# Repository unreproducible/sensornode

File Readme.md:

# SensorNode - Development Board

This is a board mostly intended to make a high quality environmental sensor
(BME280 or BME680) available via the magic of "IoT".  The board has some
interesting features that should make it good for training, teaching, or just
general IoT uses:
* ESP32
    * Wifi
    * Bluetooth
    * 4MB Flash
* BME280 / BME680 Support
  * Temperature
  * Pressure 
  * Humidity
* TSL2591
    * Full Spectrum Light Sensor
    * IR Spectrum Light Sensor
* MicroSD card slot
* LiPo battery support (charging and discharging)
* CP2104 USB <-> Serial Port
* Working Good Display E-ink support (specifically 2.13in screens)
    * v1.2 or later

# Getting Started
The following link is a presentation that was done in 2018 specifically targetting this board

https://events.linuxfoundation.org/wp-content/uploads/2017/12/osseu18_-_discovering_tiny_snakes_John-Hawley.pdf

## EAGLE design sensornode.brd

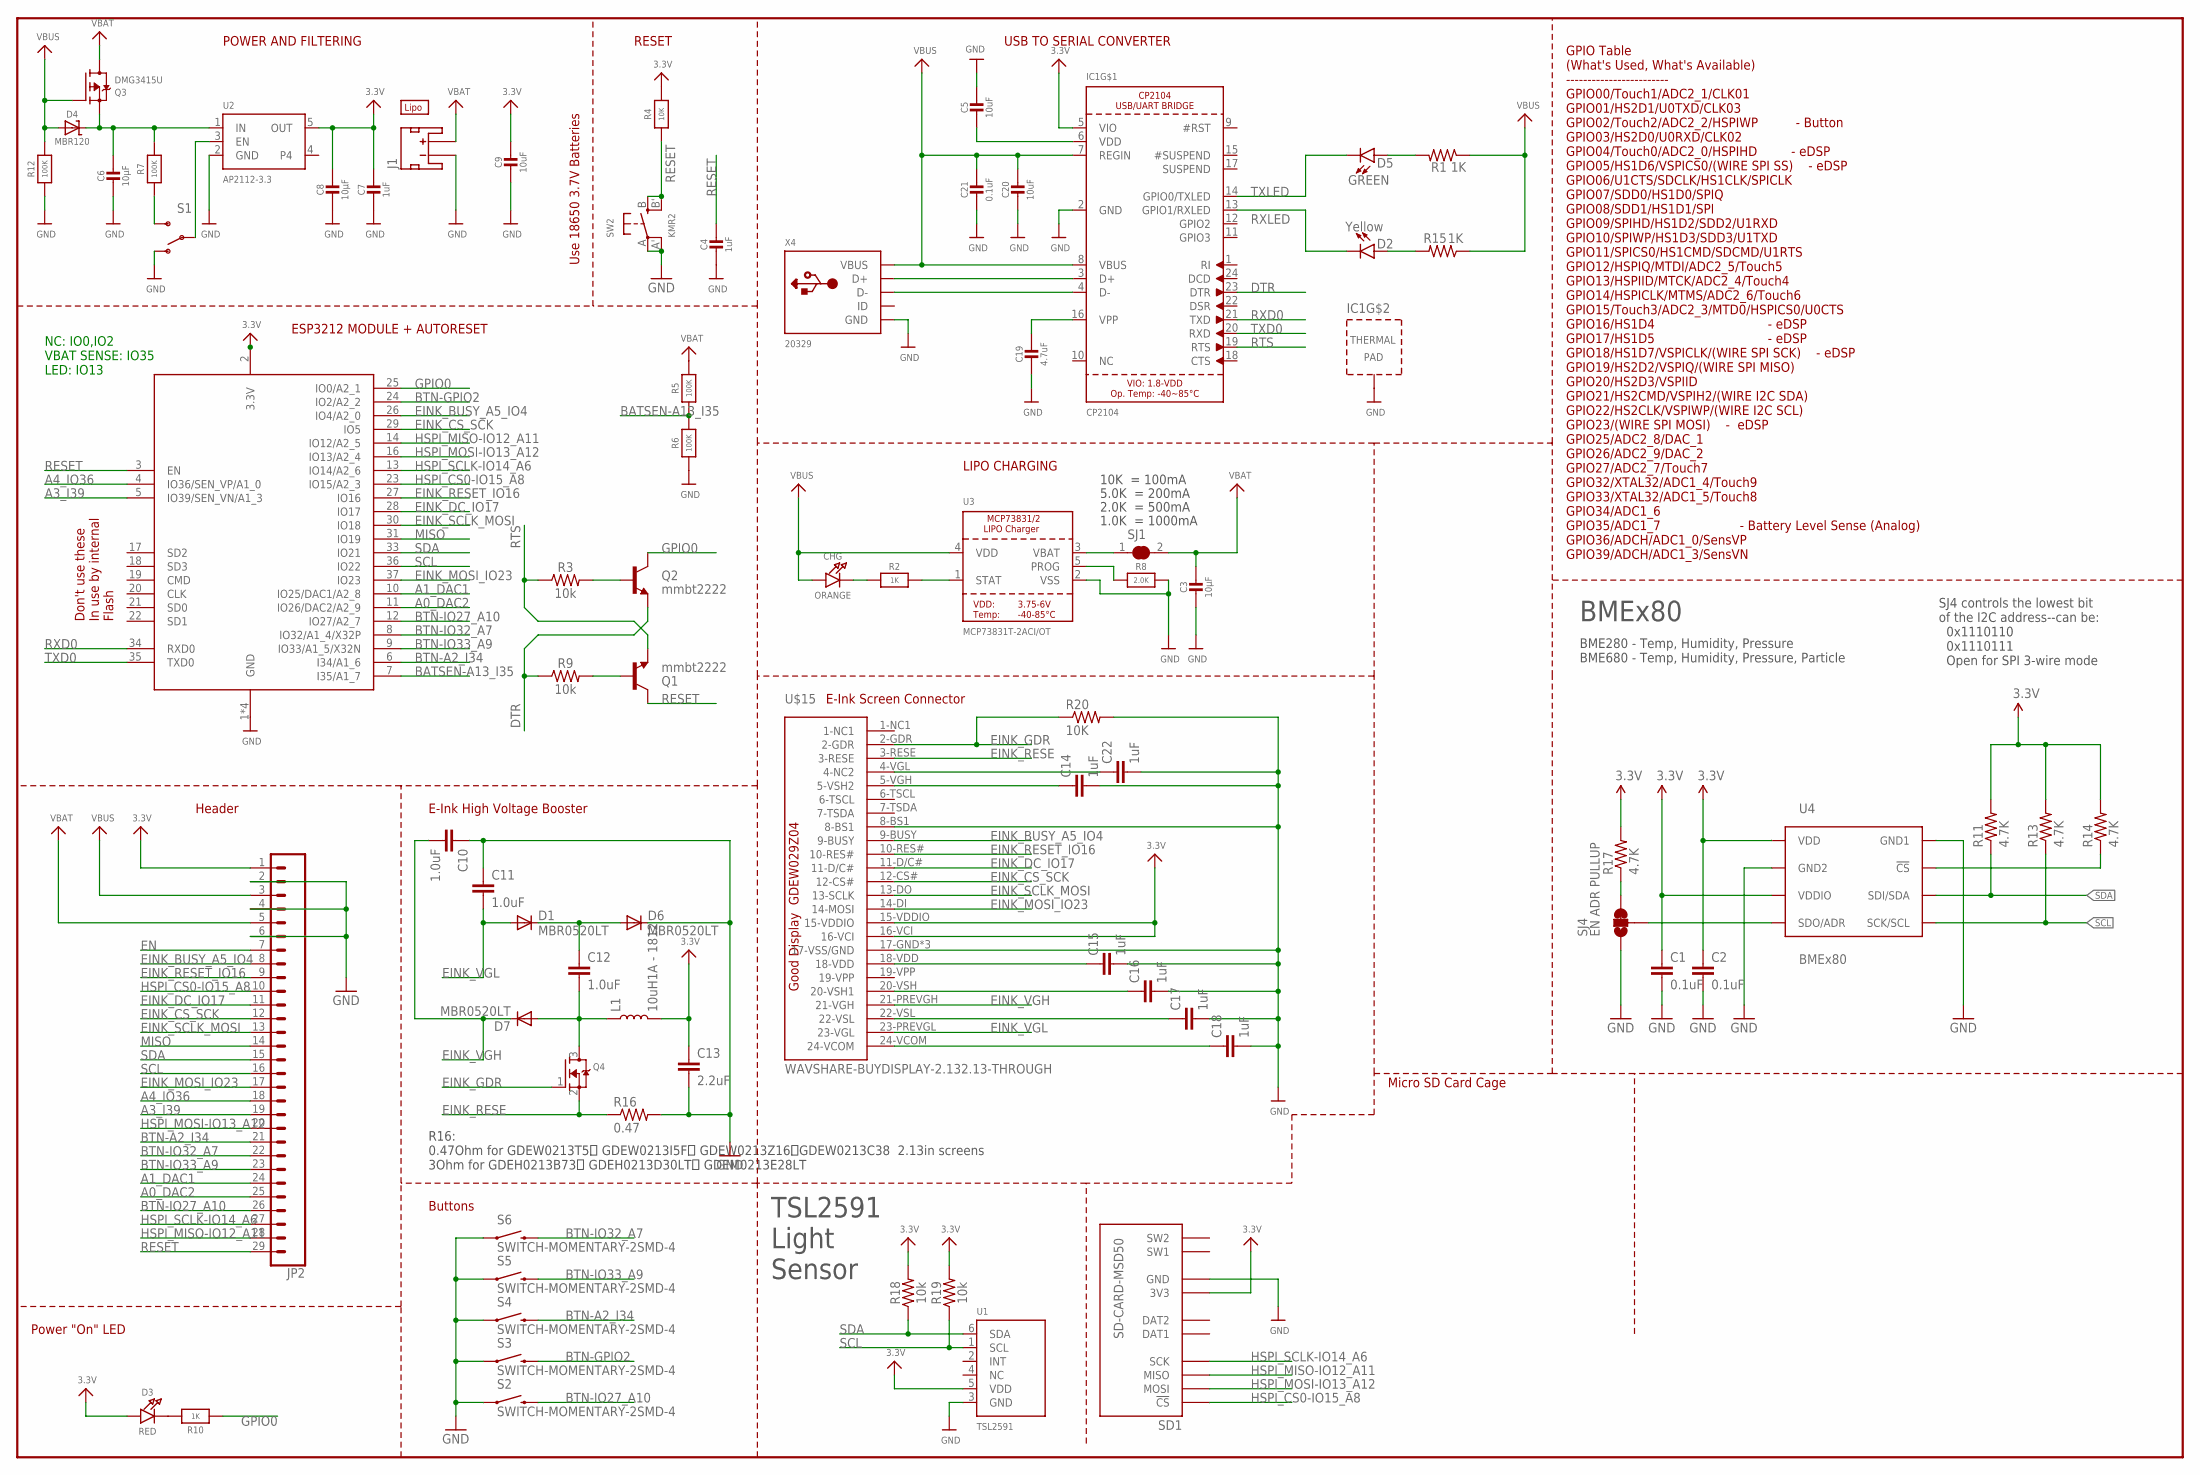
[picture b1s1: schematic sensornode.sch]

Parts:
BT1: LIPO-OUTLINE2000; LIPO-2000
C1, C2: 0.1uF; 0603-CAP
C3, C6, C8: 10µF; 0805-NO
C4, C7: 1uF; 0603-NO
C5, C9, C20: 10uF; 0805-NO
C10, C11, C12: 1.0uF; 0603
C13: 2.2uF; 0603
C14, C15, C16, C17, C18, C22: 1uF; 0603-CAP
C19: 4.7uF; 0805-NO
C21: 0.1uF; 0805-NO
CHG: ORANGE; CHIPLED_0805_NOOUTLINE
D1, D6, D7: MBR0520LT; SOD123
D2: Yellow; LED-0603
D3: RED; CHIPLED_0805_NOOUTLINE
D4: MBR120; SOD-123
D5: GREEN; LED-0603
IC1: CP2104; QFN24_4MM_SMSC
J1: JST_2MM_MALE; JST-2-SMD
JP2: CONN_29; 1X29
L1: 10uH1A - 1812; 1815
Q1, Q2: mmbt2222; SOT23-3
Q3: DMG3415U; SOT23-R
Q4: MOSFET-NREFLOW; SOT23
R1, R15: 1K; 0603-RES
R2, R10: 1K; 0603-NO
R3, R9, R18, R19: 10k; 0603
R4: 10K; 0603-NO
R5, R6, R7, R12: 100K; 0603-NO
R8: 2.0K; 0603-NO
R11, R13, R14, R17: 4.7K; 0603-RES
R16: 0.47; 0603-RES
R20: 10K; 0603-RES
S1: SWITCH-SPDT-SMD-A; SWITCH-SPST-SMD-A
S2, S3, S4, S5, S6: SWITCH-MOMENTARY-2SMD-4; TACTILE_SWITCH_TALL
SD1: SD-CARD-MSD50; SD_5031821853
SJ1: SOLDERJUMPER_CLOSED; SOLDERJUMPER_CLOSEDWIRE@1
SJ4: EN ADR PULLUP; PAD-JUMPER-3-2OF3_NC_BY_TRACE_YES_SILK_FULL_BOX
SW2: KMR2; BTN_KMR2_4.6X2.8
U1: TSL2591; DFN6_TAOS
U2: AP2112-3.3; SOT23-5
U3: MCP73831T-2ACI/OT; SOT23-5
U4: BMEx80; BME280_LGA
U$15: WAVSHARE-BUYDISPLAY-2.132.13-THROUGH; WAVSHARE-BUYDISPLAY-2.13-THM
X2: ESP32_WROOM32_SKINNY; WROOM32_SKINNY
X4: 20329; MICRO-USB5+6P-SMD-0.65-B

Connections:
3.3V: C1.1, C2.1, C7.1, C8.1, C9.1, C13.1, D3.A, IC1.5 (VIO), JP2.1, L1.2, R1.1, R4.2, R11.2, R13.2, R14.2, R15.1, R17.2, R18.2, R19.2, SD1.VCC (3V3), U1.5 (VDD), U2.5 (OUT), U4.P$6 (VDDIO), U4.P$8 (VDD), U$15.15-VDDIO, U$15.16-VCI, X2.2 (3.3V)
!CS: R14.1, U4.P$2 (!CS)
A0_DAC2: JP2.25, X2.11 (IO26/DAC2/A2_9)
A1_DAC1: JP2.24, X2.10 (IO25/DAC1/A2_8)
A3_I39: JP2.19, X2.5 (IO39/SEN_VN/A1_3)
A4_IO36: JP2.18, X2.4 (IO36/SEN_VP/A1_0)
BATSEN-A13_I35: R5.1, R6.2, X2.7 (I35/A1_7)
BTN-A2_I34: JP2.21, S4.B2 (2), X2.6 (I34/A1_6)
BTN-GPIO2: S3.B2 (2), X2.24 (IO2/A2_2)
BTN-IO27_A10: JP2.26, S2.B2 (2), X2.12 (IO27/A2_7)
BTN-IO32_A7: JP2.22, S6.B2 (2), X2.8 (IO32/A1_4/X32P)
BTN-IO33_A9: JP2.23, S5.B2 (2), X2.9 (IO33/A1_5/X32N)
DTR: IC1.23 (DTR), Q2.2 (E), R9.1
EINK_BUSY_A5_IO4: JP2.8, U$15.9-BUSY, X2.26 (IO4/A2_0)
EINK_CS_SCK: JP2.12, U$15.12-CS#, X2.29 (IO5)
EINK_DC_IO17: JP2.11, U$15.11-D/C#, X2.28 (IO17)
EINK_GDR: Q4.1 (G), R20.1, U$15.2-GDR
EINK_MOSI_IO23: JP2.17, U$15.14-DI (14-MOSI), X2.37 (IO23)
EINK_RESE: Q4.2 (S), R16.1, U$15.3-RESE
EINK_RESET_IO16: JP2.9, U$15.10-RES#, X2.27 (IO16)
EINK_SCLK_MOSI: JP2.13, U$15.13-DO (13-SCLK), X2.30 (IO18)
EINK_VGH: C10.2, D7.C, U$15.21-PREVGH (21-VGH)
EINK_VGL: C11.2, D1.A, U$15.23-PREVGL (23-VGL)
EN: JP2.7, S1.2, U2.3 (EN)
GND: C1.2, C2.2, C3.2, C4.2, C5.1, C6.2, C7.2, C8.2, C9.2, C10.1, C11.1, C13.2, C14.2, C15.2, C16.2, C17.2, C18.2, C19.2, C20.2, C21.2, C22.2, D6.C, IC1.2 (GND), IC1.THERM (TP), J1.1 (-), JP2.2, JP2.4, JP2.6, R6.1, R8.2, R12.1, R16.2, R20.2, S1.1 (O), S2.A2 (1), S3.A2 (1), S4.A2 (1), S5.A2 (1), S6.A2 (1), SD1.GND, SJ4.1, SW2.A, SW2.A' (P1), U1.3 (GND), U2.2 (GND), U3.2 (VSS), U4.P$1 (GND1), U4.P$7 (GND2), U$15.8-BS1, U$15.17-GND (17-VSS/GND), U$15.25 (17-VSS/GND), U$15.26 (17-VSS/GND), X2.1 (GND), X2.15 (GND), X2.38 (GND), X2.P$1 (GND), X4.5 (GND), X4.S1 (GND), X4.S2 (GND), X4.S3 (GND), X4.S4 (GND), X4.S5 (GND), X4.S6 (GND)
GPIO0: Q2.3 (C), R10.1, X2.25 (IO0/A2_1)
HSPI_CS0-IO15_A8: JP2.10, SD1.CS (!CS), X2.23 (IO15/A2_3)
HSPI_MISO-IO12_A11: JP2.28, SD1.MISO, X2.14 (IO12/A2_5)
HSPI_MOSI-IO13_A12: JP2.20, SD1.MOSI, X2.16 (IO13/A2_4)
HSPI_SCLK-IO14_A6: JP2.27, SD1.SCK, X2.13 (IO14/A2_6)
MISO: JP2.14, X2.31 (IO19)
unnamed: CHG.C, R2.1
unnamed: R8.1, U3.5 (PROG)
unnamed: R2.2, U3.1 (STAT)
unnamed: R7.1, S1.3 (S)
unnamed: D3.C, R10.2
unnamed: C5.2, IC1.6 (VDD)
unnamed: C6.1, D4.C, Q3.2 (S), R7.2, U2.1 (IN)
unnamed: D5.A, R1.2
unnamed: SJ1.1, U3.3 (VBAT)
unnamed: D2.A, R15.2
unnamed: C12.1, D1.C, D6.A
unnamed: Q1.1 (B), R9.2
unnamed: Q2.1 (B), R3.2
unnamed: C12.2, D7.A, L1.1, Q4.3 (D)
unnamed: R17.1, SJ4.3
unnamed: C15.1, U$15.18-VDD
unnamed: C16.1, U$15.20-VSH (20-VSH1)
unnamed: C17.1, U$15.22-VSL
unnamed: C18.1, U$15.24-VCOM
unnamed: C14.1, U$15.5-VGH (5-VSH2)
unnamed: C19.1, IC1.16 (VPP)
unnamed: C22.1, U$15.4-VGL (4-NC2)
RESET: C4.1, JP2.29, Q1.3 (C), R4.1, SW2.B (S), SW2.B' (S1), X2.3 (EN)
RTS: IC1.19 (RTS), Q1.2 (E), R3.1
RXD0: IC1.21 (TXD), X2.34 (RXD0)
RXLED: D2.C, IC1.13 (GPIO1/RXLED)
SCL: JP2.16, R13.1, R19.1, U1.1 (SCL), U4.P$4 (SCK/SCL), X2.36 (IO22)
SDA: JP2.15, R11.1, R18.1, U1.6 (SDA), U4.P$3 (SDI/SDA), X2.33 (IO21)
SDO/ADR: SJ4.2, U4.P$5 (SDO/ADR)
TXD0: IC1.20 (RXD), X2.35 (TXD0)
TXLED: D5.C, IC1.14 (GPIO0/TXLED)
USBD_N: IC1.4 (D-), X4.2 (D-)
USBD_P: IC1.3 (D+), X4.3 (D+)
VBAT: C3.1, J1.2 (+), JP2.5, Q3.3 (D), R5.2, SJ1.2
VBUS: C20.1, C21.1, CHG.A, D4.A, IC1.7 (REGIN), IC1.8 (VBUS), JP2.3, Q3.1 (G), R12.2, U3.4 (VDD), X4.1 (VBUS)

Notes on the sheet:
POWER AND FILTERING
RESET
10K = 100mA
5.0K = 200mA
2.0K = 500mA
1.0K = 1000mA
USB TO SERIAL CONVERTER
LIPO CHARGING
Power "On" LED
GPIO Table (What's Used, What's Available) ------------------------ GPIO00/Touch1/ADC2_1/CLK01 GPIO01/HS2D1/U0TXD/CLK03 GPIO02/Touch2/ADC2_2/HSPIWP - Button GPIO03/HS2D0/U0RXD/CLK02 GPIO04/Touch0/ADC2_0/HSPIHD - eDSP GPIO05/HS1D6/VSPICS0/(WIRE SPI SS) - eDSP GPIO06/U1CTS/SDCLK/HS1CLK/SPICLK GPIO07/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
Header
Buttons
Use 18650 3.7V Batteries
ESP3212 MODULE + AUTORESET
NC: IO0,IO2 VBAT SENSE: IO35 LED: IO13
Don't use these In use by internal Flash
E-Ink High Voltage Booster
TSL2591 Light Sensor
BMEx80
SJ4 controls the lowest bit of the I2C address--can be: 0x1110110 0x1110111 Open for SPI 3-wire mode
BME280 - Temp, Humidity, Pressure BME680 - Temp, Humidity, Pressure, Particle
E-Ink Screen Connector
Micro SD Card Cage
R16: 0.47Ohm for GDEW0213T5、 GDEW0213I5F、 GDEW0213Z16、GDEW0213C38 2.13in screens 3Ohm for GDEH0213B73、 GDEH0213D30LT、 GDEM0213E28LT

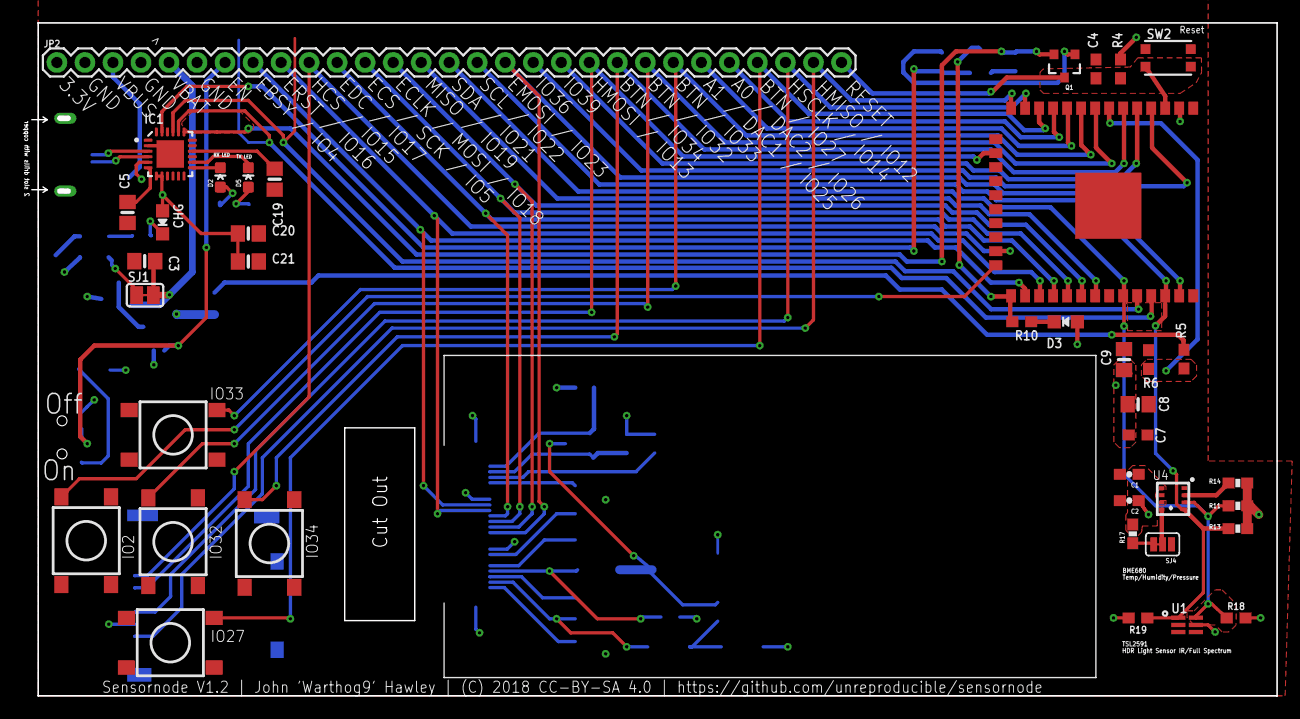
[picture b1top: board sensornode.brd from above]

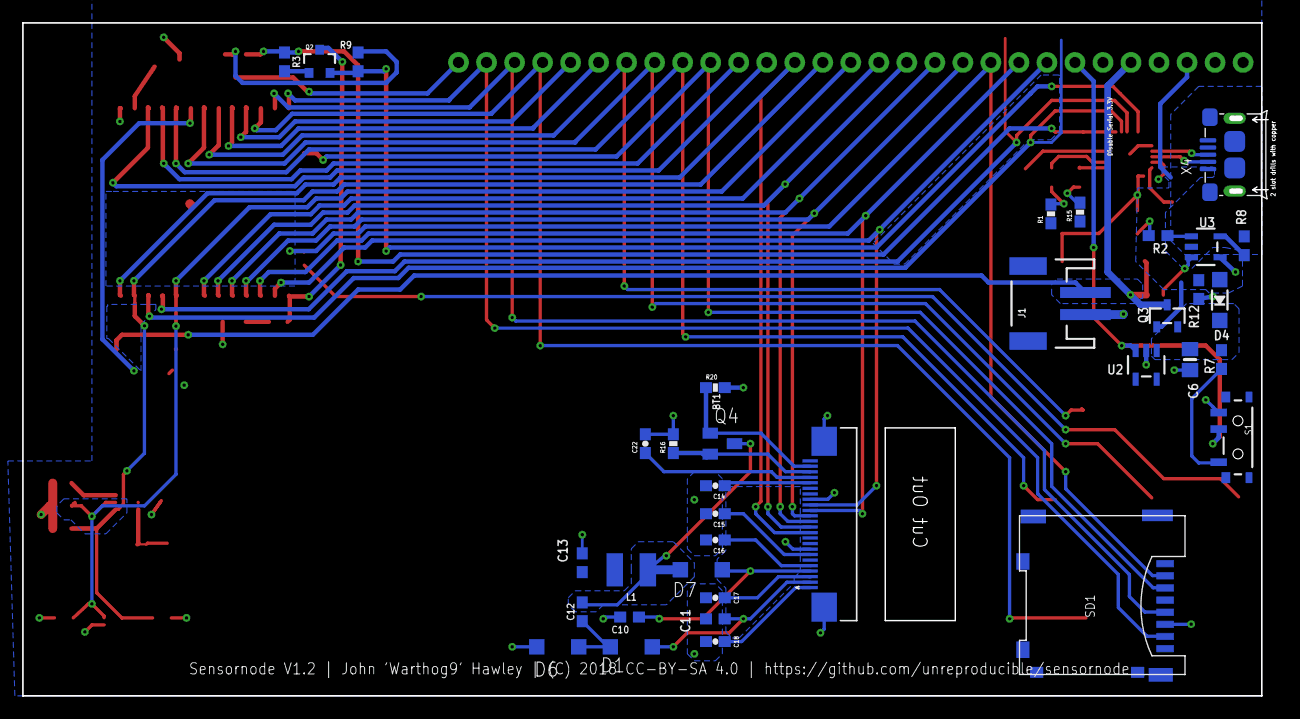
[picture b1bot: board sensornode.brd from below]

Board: 2 copper layers, 112.9 x 61.0 mm, 76 parts (36 on the bottom side), 66 nets.

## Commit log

2016-12-18 Adding the schematic
2016-12-19 Updating schematic, and initial layout
2016-12-19 Updating with latest routing attempt
2016-12-19 Fixing ear routing
    it's tighter now, but it's a lot better for obvious reasons
2016-12-20 Reworking things + the ESP12S is lacking pins present on the schematic (doh)
2016-12-20 Finishing up for the night, think this is all routed now
2016-12-20 more cleanups
2016-12-24 Adding in the colateral used for the silkscreen
2016-12-24 Finally moved things around enough to make it all work
2016-12-25 Just adding some silk
2016-12-25 more silkscreen stuff
2016-12-25 clearing out all the stupid # files
2016-12-27 more silk changes
2017-01-07 Initial sensor board work
2017-06-27 Initial commit for ESP32 conversion
2018-02-05 Initial, full, routing - minus Sensors, update gitignore
2018-02-15 Mostly Routed - saving and pushing up
2018-03-10 Big changes - 'final' routing, light sensor, bme280 -> bme680
2018-03-10 Renaming the board and schematic to actually match the project
2018-03-10 Updating the License information
2018-03-10 Cleaning up some text
2018-03-10 Board: Show all layers
2018-03-10 Adding board image and pdf schematic
2018-03-11 Adjusting parts based on BOM generation
    So there were a bunch of duplicated 0603 and 0805 parts, unifying
    things to 0603s
2018-03-28 USB-UART: switch to "USB Powered"
    This changes the USB chip from being powered via the
    regulated 3.3V line off the board, to being powered
    via the USB VBUS power. This should basically disable
    the chip when the USB isn't plugged in.
2018-04-02 BRD: updating the accepted DRC issues
2018-04-05 Adjusting the keepout around the antennae
2018-04-06 USB: Swapping the USB part out - twas unobtanium
    the 4UCONN connector that Adafruit used is basically made of unobtanium
    and more or less doesn't exist. The part that was trying to be used
    the rear prongs did not match up by any stretch of the imagination.
    A mess of e-mails an annoyance ensued.
    I'm swapping out the part on everything I can now, this seems to be
    more common, and there's parts that are similar enough to it that
2018-04-25 Moving sensors down-making room for wifi keep out
2018-04-25 Clearing some space around the eink screen
2018-04-25 increase board height to 61mm
    Also adjust some parts near the top
2018-04-25 Adjusting board width
2018-05-06 Getting the updates in
    Yes, this is a terrible commit
2018-05-14 Adjusting some signal names
2018-07-17 Moving vias out from under FPC connector
2018-07-17 Moving traces around the FPC connector
2018-07-17 Adding SD Card
2018-07-17 Redoing the buttons
2018-07-30 Updating the FPC + part for the e-ink screen
    Think I had the pinout on the FPC backwards. This should flip it
    and move a bunch of pieces around as a result
2018-08-04 Adding a 10uF Cap to the CP2104
    This make it more closely resemble the known working designs.
    Getting paranoid due to when this will need to get built.
2018-08-08 Cleaning up a bunch of stuff
2018-08-14 Final cleanups going to prototype v2
2018-08-16 Swapping out microSD cage for the Molex
    The 4UConn cage is delightlyfully cheap, but the lead times are
    dicey. At least for this run I'm going to go with the easily
    found, but more expensive, card cage, and I'll revert when
    I've got more time on a different production run.
2018-10-23 Updating the Readme
2018-10-23 Adding Image of SensorNode v1.1, top looking
2021-04-02 Adjusting e-ink screen, and reving to v1.2
    So this adds C22, a 1uF cap on VGL and R20 to EINK_GDR. These
    fall in line with what's on the waveshare and Open Hardware Summit
    badge and should be slightly more reliable than my current circuit
2021-04-02 Removing the backup FTDI port
    As it turns out my luck with the power changes to the serial port
    chip worked just fine, and as a result the FTDI header is actually
    extraneous and obnoxious. Remove it, get the board a little
    smaller.
2021-04-02 Modifications to fix the e-ink screen drivers
    So turns out the e-ink screen needs two fixes:
    1) The inductor pad is just straight up wrong, so I've replaced that
    1.1) I've also moved from a 68uH coil to a 10uH1A coil (matching Good
    Display's DESPI-C02 more closely)
    2) The R16 resistor should not, in fact, be 2.2Ohm, it should be 0.47Ohm
    (though I'll note 1Ohm works)
2021-04-02 Updating Readme.md to include link to discovering tiny snakes from 2018
    Updating Readme.md to include link to discovering tiny snakes from 2018
2021-04-02 Readme.md: note that the e-ink screen is now supported
    Since I've got the e-ink screen *WORKING* finally, might as well advertise it
2021-04-20 Schematic: Updating to latest version
    This updates the schematic to the latest version

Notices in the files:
sensornode.brd:
Sensornode V1.2 | John 'Warthog9' Hawley | (C) 2018 CC-BY-SA 4.0 | https://github.com/unreproducible/sensornode
parts and their libraries:
microbuilder: This work is placed in the public domain, and may be freely used for commercial and non-commercial work with the following conditions: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
SparkFun-LED: Licensing: Creative Commons ShareAlike 4.0 International - https://creativecommons.org/licenses/by-sa/4.0
